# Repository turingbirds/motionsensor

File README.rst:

motionsensor
============

Microwave doppler effect motion sensor

Features
--------

- USB-powered (150 mA)
- Wakes up host computer on alarm (USB remote wakeup)
- Standalone operation (no PC or USB host required)
- Live velocity (IF) monitoring via USB audio stream to PC
- Automatic gain control
- Data logging
- Driverless operation: tested on Windows XP, Windows 7, Ubuntu GNU/Linux 14.04

..	

.. image:: doc/motionsensor2.jpeg
   :width: 1280
   :height: 780
   :scale: 60%
   :align: center

.. image:: doc/motionsensor3.jpeg
   :width: 1280
   :height: 780
   :scale: 60%
   :align: center

.. image:: doc/motionsensor1.jpeg
   :width: 1280
   :height: 780
   :scale: 60%
   :align: center

.. image:: doc/pcb.png
   :width: 1280
   :height: 811
   :scale: 60%
   :align: center

|

.. image:: doc/frontend_transfer_function.png
   :width: 846
   :height: 363
   :scale: 90%
   :align: center

|

.. image:: doc/doppler_log.png
   :width: 824
   :height: 386
   :scale: 93%
   :align: center

|

.. image:: doc/doppler_radio.png
   :width: 824
   :height: 414
   :scale: 93%
   :align: center

.. class:: center

All photos thanks to `Dennis van Zuijlekom <https://www.flickr.com/photos/dvanzuijlekom/>`_ at `Hack42 <http://www.hack42.nl>`_!

User guide
==========

Overview
--------

The device is based around a compact radar module. Radar waves penetrate glass and other materials, allowing the device to operate completely hidden from sight, unlike traditional passive infrared (PIR) motion detectors. The principle of operation for motion detection is the doppler effect. The module acts simultaneously as a sender and receiver of radar waves. Part of the emitted waves are reflected in the environment and fall back onto the sensor. If, meanwhile, an object in the environment has a motion component normal to the sensor, a doppler shift will be introduced in the reflected radio waves, proportional to the velocity of the object. The resulting frequency change (between emitted and received frequency) is demodulated by the module and output as a signal in the audio band. The rest of the device amplifies this signal and digitises it for further processing with the microcontroller and (optionally) relay to a connected USB host as an audio stream.

Many radar modules are commercially available for less than $10. This repository contains all the information necessary to build a complete USB/standalone motion detector based on such a module.

USB operation
-------------

The device uses a USB Interface Association Descriptor [1]_ to identify itself as (1) a standard HID-compliant mouse and (2) a standard USB streaming audio device. Only the HID can wake the computer.

Standalone operation
--------------------

The motion sensor does not require a USB host and can operate in standalone mode. For independent operation, supply power (4.5..14 V) via the USB GND and Vcc terminals.

When the alarm is raised, the USB D- line will be driven to +3.3V for at least 10 ms, after which it will return to a floating condition. The output impedance is at least 22 Ω due to the USB series resistor. If this line is used to drive external devices, it is advised to add a modest pull-down resistor (e.g. 4k7).

Host audio
==========

Linux
-----

In case of conflicts, remove interfering kernel drivers:

::

	sudo rmmod snd_usb_audio
	sudo rmmod snd_usbmidi_lib

Set volume levels and such:

::

	alsamixer

Find the motion sensor device:

::

	arecord -l

*Recording from the device:*

::

	arecord -f S16_LE -r 8000 -t raw -v -D hw:1,0 > foo.pcm

*Listening to the device:* This assumes that you are using pulseaudio.

::

	pactl load-module module-loopback latency_msec=1	

Windows XP
----------

*Recording from the device:* native, select "Microwave Doppler Sensor" as audio source

*Listening to the device:* Download "Virtual Audio Cable" [2]_ and use the "Audio Repeater" tool. Lag is at least 50 ms.

Windows 7
---------

*Recording from the device:* native

*Listening to the device:* native. Use "Listen to device" under [taskbar speaker icon] → Recording devices → Microwave Doppler Sensor → Properties → Listen → Listen to this device.

Host power management
=====================

N.B. USB wake needs to be enabled in BIOS

Linux
-----

Suspend using:

::

	pm-suspend

Find device in tree:

::

	grep -r Microwave /sys/devices/pci0000\:00/

In the ``power`` directory of the device, you'll find a file called ``wakeup``. Write "enabled" to this file, e.g.:

::

	echo "enabled" > /sys/devices/pci0000:00/0000:00:14.0/usb2/2-2/power/wakeup

Make sure to enable upstream hubs as well.

N.B. Add the commands in this section to ``/etc/rc.local`` to enable the wake-from-standby feature on boot.

Windows
-------

Enable "Allow device to wake computer from suspend" in the device manager properties of the HID-compatible mouse that is a part of the Microwave Doppler Sensor.

Developer's guide
=================

Frontend
--------

The frontend consists of a high-gain low-noise amplifier chain that is built using three dual op-amp ICs. The maximum theoretical voltage gain is 1.3·10\ :sup:`5` (100 dB). An 8-bit digital potentiometer after the second gain stage is configured as an attenuator and acts as gain control, with a dynamical range of 30 dB. The complete analog front-end is powered by a ±5V bipolar rail that is generated by an on-board boost converter. After amplification and filtering the signal is offered to a 12-bit ADC running at an 8 kHz sampling rate and 3.3 V reference voltage.

Data acquisition and USB communication is performed by an STM32F103 microcontroller. When connected to a USB host, the digital potentiometer setlevel is controlled by the volume setlevel of the device. When the volume is set to 100%, automatic gain control (AGC) is enabled. When not connected to USB, the potentiometer is set to a fixed value so that the frontend gain is high.

N.B. the AGC aliasing filter should be designed for one bit of noise at half the sampling rate, i.e. max. 0.81 mV @ 4 kHz (3.3 V across 12 bits = 0.81 mV/bit)

Firmware notes
--------------

For volume scale (how to map bits to decibels), see e.g. [3]_.

Schematic
---------

`Schematic (.pdf) <doc/motionsensor_schematic.pdf>`_

PCB
---

All discrete components are 0603.

- Dimensions: 78 x 49 mm
- Layers: 4 (two inner ground planes)
- Thickness: 1.2 mm

Enclosure and mounting
----------------------

Vertical cross-section:

::

	----USB/USER INTERFACE----
	- 5 mm plastic inserts (1.0 mm margin)
	- 1.2 mm main PCB
	- 5 mm bus
	- 1.2 mm shield PCB
	- 0.2 mm washer
	----DOPPLER UNIT----
	Total: 12 mm

Screw length: 12 mm
Screw diameter: 2.5 mm

N.B. Doppler module is <7 mm

Bill of materials
-----------------

`Bill of materials (.csv) <doc/bill_of_materials.csv>`_

References
==========

.. [1] USB Complete Fourth Edition: The Developer's Guide (4th edition). Jan Axelson, publisher: Lakeview Research. June 1, 2009
.. [2] `Virtual Audio Cable \<http://software.muzychenko.net/eng/vac.htm\> <http://software.muzychenko.net/eng/vac.htm>`_
.. [3] `USB audio device volume scale \<https://msdn.microsoft.com/en-us/library/windows/hardware/ff537309\> <https://msdn.microsoft.com/en-us/library/windows/hardware/ff537309(v=vs.85).aspx>`_

License
=======

`Open source hardware <https://www.oshwa.org/>`_ is hardware for which the design is made publicly available, so that anyone can study, modify, distribute, make, and sell the design or hardware based on that design, subject to the following license conditions.

Hardware licensed under the *CERN Open Hardware Licence Version 2 - Weakly Reciprocal,* a copy of which is included in this repository at `cern_ohl_w_v2.txt <https://github.com/turingbirds/motionsensor/blob/master/cern_ohl_w_v2.txt>`_.

Software licensed under the *Apache License 2.0,* a copy of which is included at `apache_license_2.0.txt <https://github.com/turingbirds/motionsensor/blob/master/apache_license_2.0.txt>`_.

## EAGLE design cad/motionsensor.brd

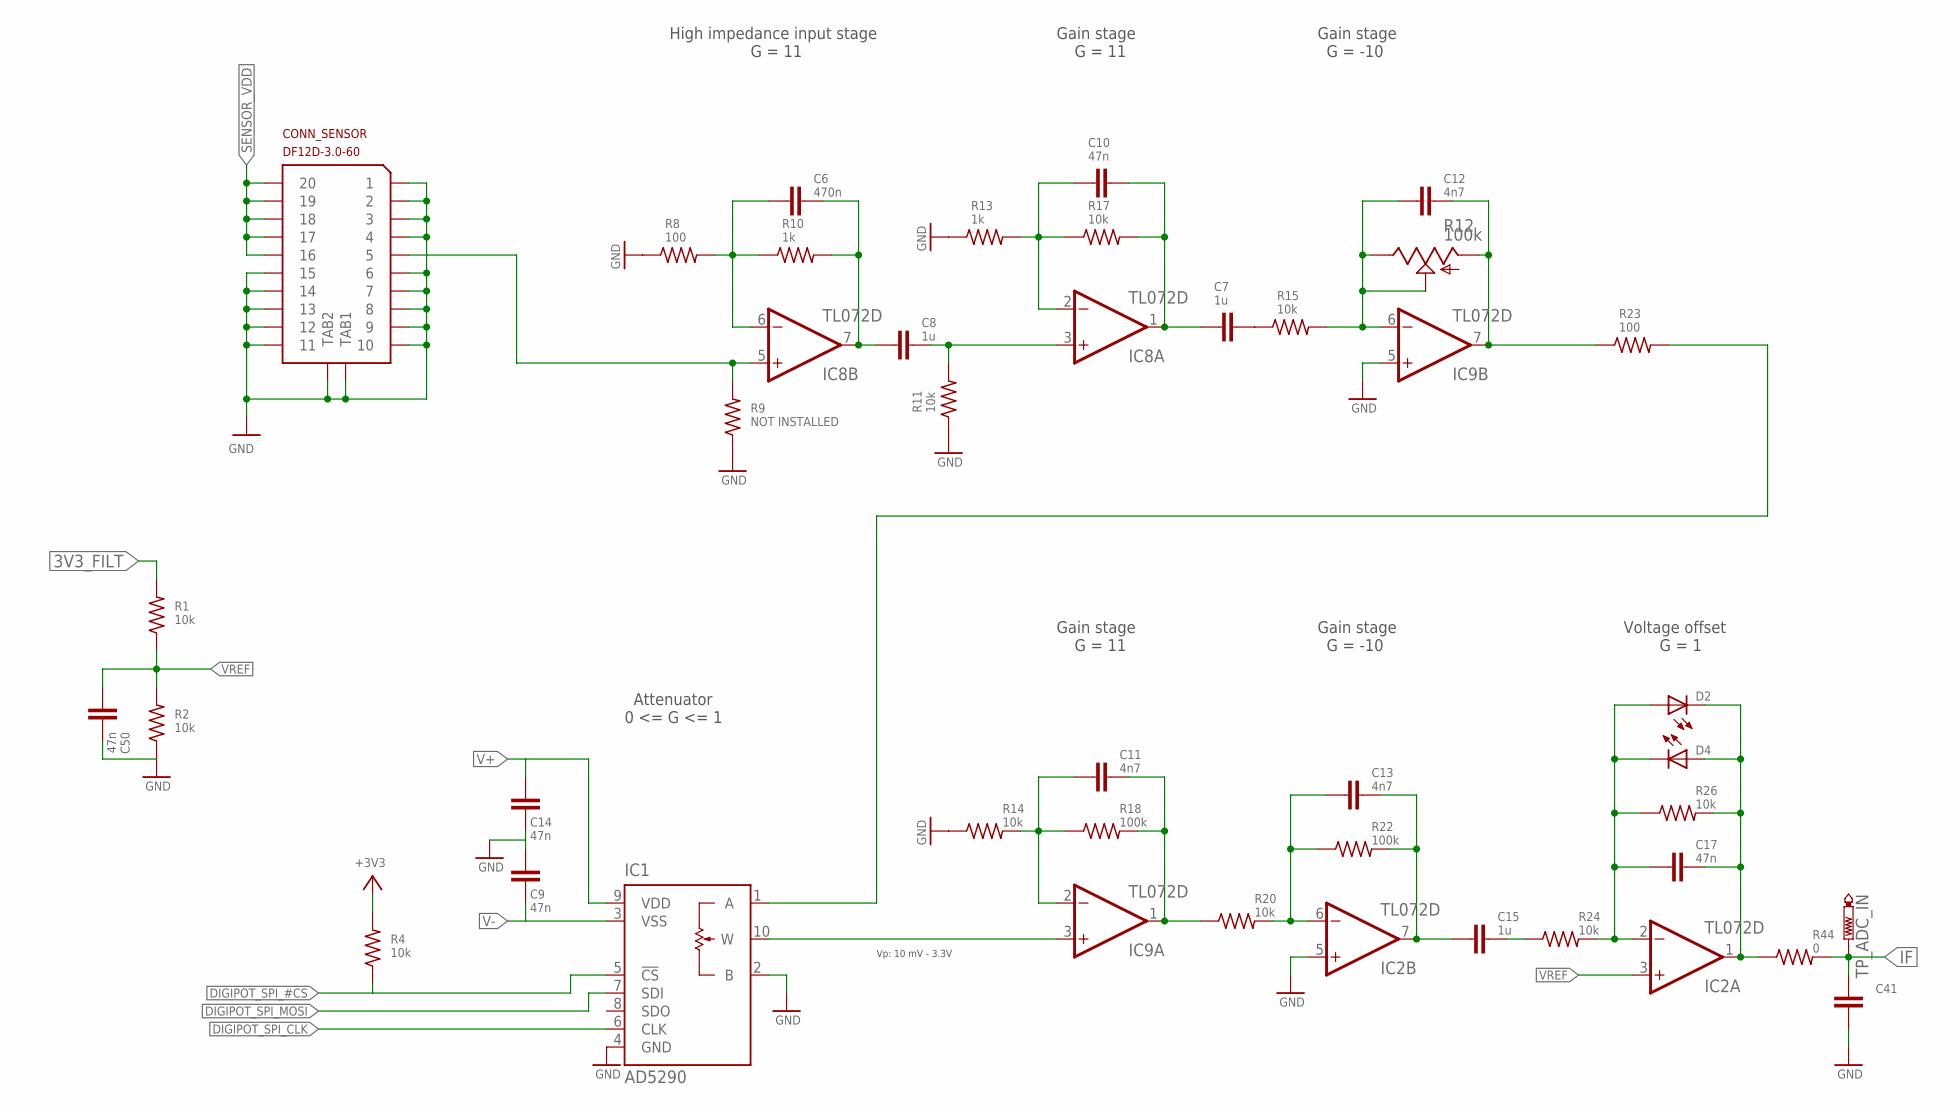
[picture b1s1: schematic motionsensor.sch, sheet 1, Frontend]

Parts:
C6: 470n; C0603
C7, C8, C15: 1u; C0603
C9, C10, C14, C17, C50: 47n; C0603
C11, C12, C13: 4n7; C0603
C41: C-EUC0603; C0603
CONN_SENSOR: DF12D-3.0-60; DF12-3.0-60
D2, D4: LEDCHIPLED_0603; CHIPLED_0603
IC1: AD5290; MSOP10
IC2, IC8, IC9: TL072D; SO08
R1, R2, R4, R11, R14, R15, R17, R20, R24, R26: 10k; R0603
R8, R23: 100; R0603
R9: NOT INSTALLED; R0603
R10, R13: 1k; R0603
R12: 100k; 3223G
R18, R22: 100k; R0603
R44: 0; R0603
TP_ADC_IN: PTR1B1,27; B1,27

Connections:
3V3_FILT: R1.2; also elsewhere on the board
+3V3: R4.2; also elsewhere on the board
DIGIPOT_SPI_#CS: IC1.5 (!CS), R4.1; also elsewhere on the board
DIGIPOT_SPI_CLK: IC1.6 (CLK); also elsewhere on the board
DIGIPOT_SPI_MOSI: IC1.7 (SDI); also elsewhere on the board
GND: C9.1, C14.2, C41.2, C50.2, CONN_SENSOR.P$1 (1), CONN_SENSOR.P$2 (2), CONN_SENSOR.P$3 (3), CONN_SENSOR.P$4 (4), CONN_SENSOR.P$6 (6), CONN_SENSOR.P$7 (7), CONN_SENSOR.P$8 (8), CONN_SENSOR.P$9 (9), CONN_SENSOR.P$10 (10), CONN_SENSOR.P$11 (11), CONN_SENSOR.P$12 (12), CONN_SENSOR.P$13 (13), CONN_SENSOR.P$14 (14), CONN_SENSOR.P$15 (15), CONN_SENSOR.TAB1, CONN_SENSOR.TAB2, IC1.2 (B), IC1.4 (GND), IC2.5 (+IN), IC9.5 (+IN), R2.1, R8.1, R9.1, R11.1, R13.1, R14.1; also elsewhere on the board
IF: C41.1, R44.2, TP_ADC_IN.TP; also elsewhere on the board
unnamed: C6.1, IC8.6 (-IN), R8.2, R10.1
unnamed: C6.2, C8.1, IC8.7 (OUT), R10.2
unnamed: CONN_SENSOR.P$5 (5), IC8.5 (+IN), R9.2
unnamed: C7.2, R15.1
unnamed: C10.1, IC8.2 (-IN), R13.2, R17.1
unnamed: C7.1, C10.2, IC8.1 (OUT), R17.2
unnamed: C8.2, IC8.3 (+IN), R11.2
unnamed: C12.1, IC9.6 (-IN), R12.2 (S), R12.3 (E), R15.2
unnamed: C12.2, IC9.7 (OUT), R12.1 (A), R23.1
unnamed: IC1.1 (A), R23.2
unnamed: C11.1, IC9.2 (-IN), R14.2, R18.1
unnamed: C11.2, IC9.1 (OUT), R18.2, R20.1
unnamed: C13.1, IC2.6 (-IN), R20.2, R22.1
unnamed: C13.2, C15.1, IC2.7 (OUT), R22.2
unnamed: C15.2, R24.1
unnamed: IC1.10 (W), IC9.3 (+IN)
unnamed: C17.1, D2.A, D4.C, IC2.2 (-IN), R24.2, R26.1
unnamed: C17.2, D2.C, D4.A, IC2.1 (OUT), R26.2, R44.1
SENSOR_VDD: CONN_SENSOR.P$16 (16), CONN_SENSOR.P$17 (17), CONN_SENSOR.P$18 (18), CONN_SENSOR.P$19 (19), CONN_SENSOR.P$20 (20); also elsewhere on the board
V+: C14.1, IC1.9 (VDD); also elsewhere on the board
V-: C9.2, IC1.3 (VSS); also elsewhere on the board
VREF: C50.1, IC2.3 (+IN), R1.1, R2.2

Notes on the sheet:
High impedance input stage
G = 11
Gain stage
G = -10
Voltage offset
G = 1
Attenuator
0 <= G <= 1
Vp: 10 mV - 3.3V

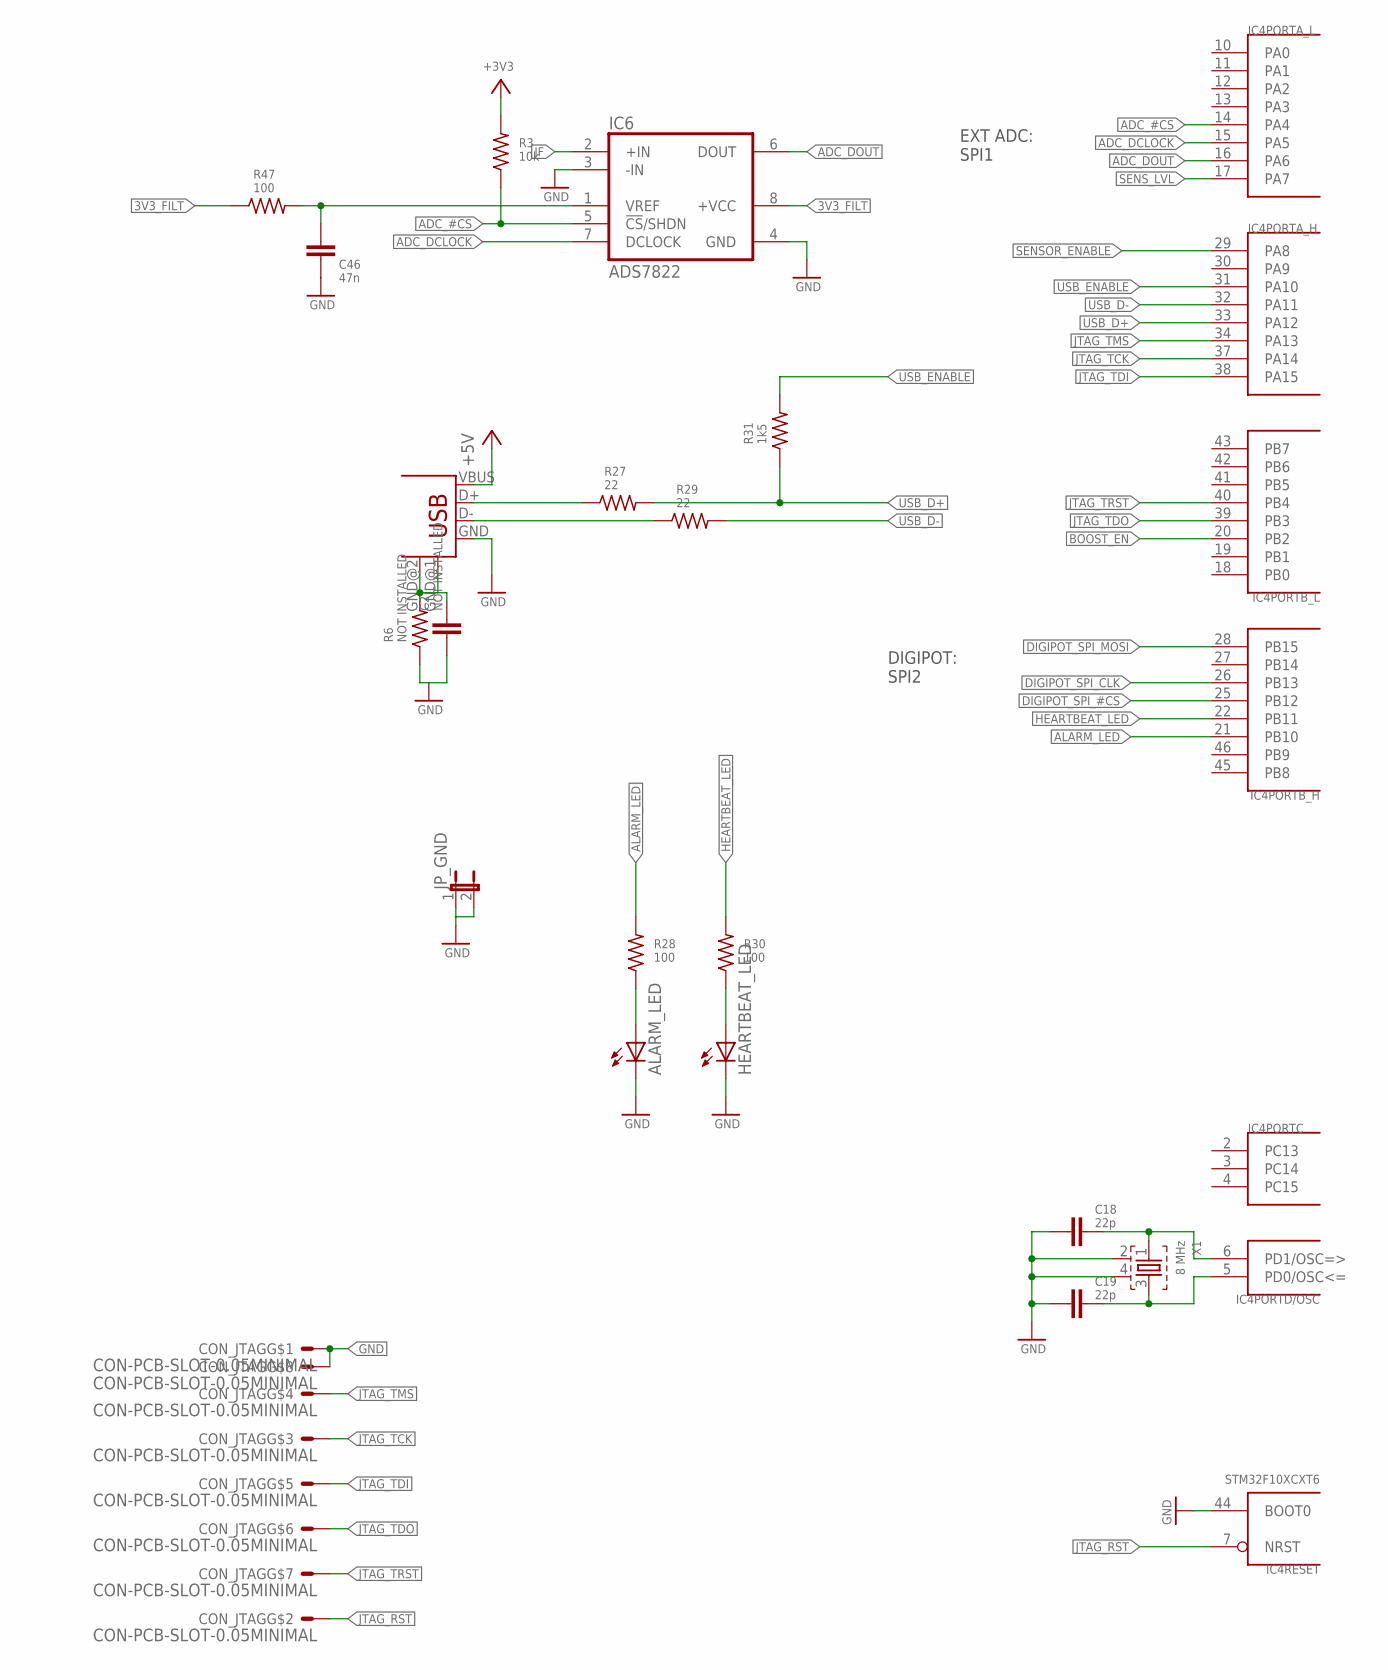
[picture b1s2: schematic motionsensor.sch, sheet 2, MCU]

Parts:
ALARM_LED: LED3MM
C2: NOT INSTALLED; C0603
C18, C19: 22p; C0603
C46: 47n; C0603
CON_JTAG: CON-PCB-SLOT-0.05MINIMAL; CONN_SLOT_MINIMAL
CON_USB: USB-VERT; USB-MB-V
HEARTBEAT_LED: LED3MM
IC4: STM32F10XCXT6; TQFP48
IC6: ADS7822; SO08
JP_GND: JP1E; JP1
R3: 10k; R0603
R6: NOT INSTALLED; R0603
R27, R29: 22; R0603
R28, R30, R47: 100; R0603
R31: 1k5; R0603
X1: 8 MHz; CTS406

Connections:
3V3_FILT: IC6.8 (+VCC), R47.1; also elsewhere on the board
+3V3: R3.2; also elsewhere on the board
ADC_#CS: IC4.14 (PA4), IC6.5 (!CS!/SHDN), R3.1
ADC_DCLOCK: IC4.15 (PA5), IC6.7 (DCLOCK)
ADC_DOUT: IC4.16 (PA6), IC6.6 (DOUT)
ALARM_LED: IC4.21 (PB10), R28.2
BOOST_EN: IC4.20 (PB2); also elsewhere on the board
DIGIPOT_SPI_#CS: IC4.25 (PB12); also elsewhere on the board
DIGIPOT_SPI_CLK: IC4.26 (PB13); also elsewhere on the board
DIGIPOT_SPI_MOSI: IC4.28 (PB15); also elsewhere on the board
GND: ALARM_LED.K (C), C2.1, C18.1, C19.1, C46.2, CON_JTAG.1, CON_JTAG.8, CON_USB.GND, HEARTBEAT_LED.K (C), IC4.44 (BOOT0), IC6.3 (-IN), IC6.4 (GND), JP_GND.1, JP_GND.2, R6.1, X1.2, X1.4; also elsewhere on the board
HEARTBEAT_LED: IC4.22 (PB11), R30.2
IF: IC6.2 (+IN); also elsewhere on the board
JTAG_RST: CON_JTAG.2, IC4.7 (NRST)
JTAG_TCK: CON_JTAG.3, IC4.37 (PA14)
JTAG_TDI: CON_JTAG.5, IC4.38 (PA15)
JTAG_TDO: CON_JTAG.6, IC4.39 (PB3)
JTAG_TMS: CON_JTAG.4, IC4.34 (PA13)
JTAG_TRST: CON_JTAG.7, IC4.40 (PB4)
unnamed: C2.2, CON_USB.GND@1 (GND), CON_USB.GND@2 (GND), R6.2
unnamed: CON_USB.D+, R27.1
unnamed: C46.1, IC6.1 (VREF), R47.2
unnamed: CON_USB.D-, R29.1
unnamed: C19.2, IC4.5 (PD0/OSC<=), X1.3
unnamed: C18.2, IC4.6 (PD1/OSC=>), X1.1
unnamed: ALARM_LED.A, R28.1
unnamed: HEARTBEAT_LED.A, R30.1
SENSOR_ENABLE: IC4.29 (PA8); also elsewhere on the board
SENS_LVL: IC4.17 (PA7)
USB_+5V: CON_USB.VBUS; also elsewhere on the board
USB_D+: IC4.33 (PA12), R27.2, R31.1
USB_D-: IC4.32 (PA11), R29.2
USB_ENABLE: IC4.31 (PA10), R31.2

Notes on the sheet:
EXT ADC: SPI1
DIGIPOT: SPI2

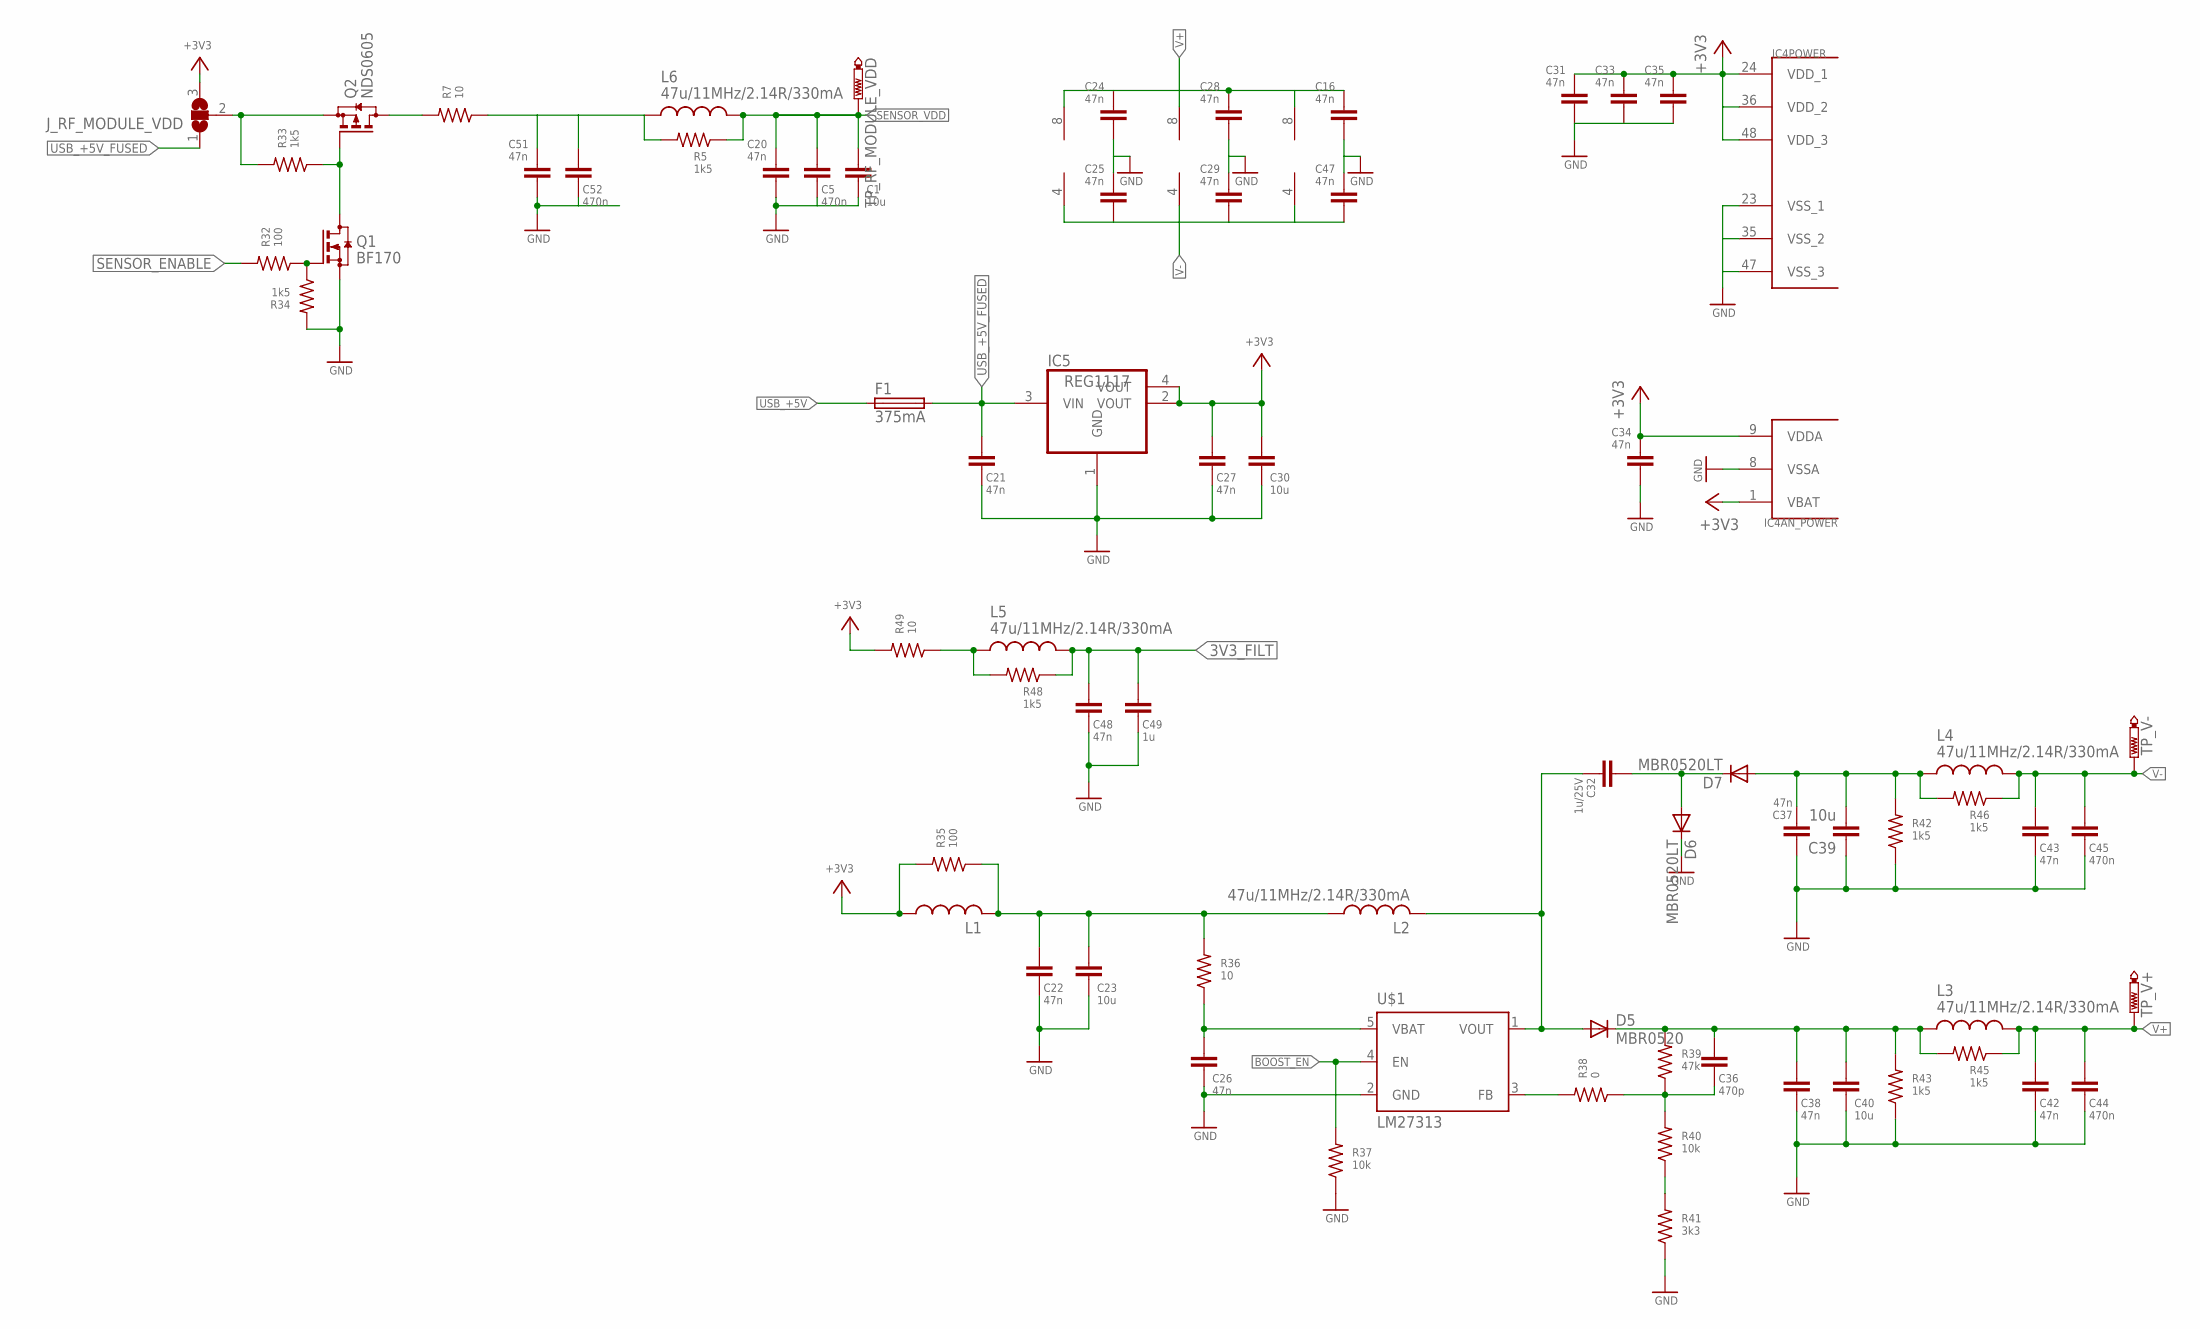
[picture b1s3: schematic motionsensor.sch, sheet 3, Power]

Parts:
C1, C23, C30, C39, C40: 10u; C1206
C5, C44, C45, C52: 470n; C0603
C16, C20, C21, C22, C24, C25, C27, C28, C29, C31, C33, C34, C35, C37, C38, C42, C43, C47, C48, C51: 47n; C0603
C26: 47n; C1206
C32: 1u/25V; C0603
C36: 470p; C0603
C49: 1u; C0603
D5: MBR0520; SOD123
D6, D7: MBR0520LT; SOD123
F1: 375mA; 0603
IC2, IC8, IC9: TL072D; SO08
IC4: STM32F10XCXT6; TQFP48
IC5: REG1117; SOT223
J_RF_MODULE_VDD: SJ2W; SJ_2
L1: L-USL2012C; L2012C
L2, L3, L4, L5, L6: 47u/11MHz/2.14R/330mA; R1210
Q1: BF170; SOT23
Q2: NDS0605; SOT23
R5, R33, R34, R42, R43, R45, R46, R48: 1k5; R0603
R7, R36, R49: 10; R0603
R32, R35: 100; R0603
R37, R40: 10k; R0603
R38: 0; R0603
R39: 47k; R0603
R41: 3k3; R0603
TP_RF_MODULE_VDD: PTR1B1,27; B1,27
TP_V+: PTR1B1,27; B1,27
TP_V-: PTR1B1,27; B1,27
U$1: LM27313; TSOP5

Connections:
3V3_FILT: C48.1, C49.1, L5.2, R48.1; also elsewhere on the board
+3V3: C27.1, C30.1, C31.2, C33.2, C34.2, C35.2, IC4.1 (VBAT), IC4.9 (VDDA), IC4.24 (VDD_1), IC4.36 (VDD_2), IC4.48 (VDD_3), IC5.2 (VOUT), IC5.4 (VOUT), J_RF_MODULE_VDD.3, L1.1, R35.2, R49.2; also elsewhere on the board
+3V3_FILT: C22.1, C23.1, L1.2, L2.1, R35.1, R36.2
BOOST_EN: R37.2, U$1.4 (EN); also elsewhere on the board
GND: C1.2, C5.2, C16.1, C20.1, C21.2, C22.2, C23.2, C24.1, C25.2, C26.2, C27.2, C28.1, C29.2, C30.2, C31.1, C33.1, C34.1, C35.1, C37.1, C38.2, C39.1, C40.2, C42.2, C43.2, C44.2, C45.2, C47.2, C48.2, C49.2, C51.1, C52.2, D6.C, IC4.8 (VSSA), IC4.23 (VSS_1), IC4.35 (VSS_2), IC4.47 (VSS_3), IC5.1 (GND), Q1.2 (S), R34.2, R37.1, R41.1, R42.1, R43.1, U$1.2 (GND); also elsewhere on the board
unnamed: J_RF_MODULE_VDD.2, Q2.2 (S), R33.2
unnamed: Q2.3 (D), R7.2
unnamed: Q1.1 (G), R32.1, R34.1
unnamed: L5.1, R48.2, R49.1
unnamed: Q1.3 (D), Q2.1 (G), R33.1
unnamed: C32.2, D5.A, L2.2, U$1.1 (VOUT)
unnamed: C26.1, R36.1, U$1.5 (VBAT)
unnamed: C32.1, D6.A, D7.C
unnamed: C36.2, R38.1, R39.1, R40.2
unnamed: R40.1, R41.2
unnamed: R38.2, U$1.3 (FB)
unnamed: C37.2, C39.2, D7.A, L4.1, R42.2, R46.2
unnamed: C36.1, C38.1, C40.1, D5.C, L3.1, R39.2, R43.2, R45.2
SENSOR_ENABLE: R32.2; also elsewhere on the board
SENSOR_VDD: C1.1, C5.1, C20.2, L6.2, R5.1, TP_RF_MODULE_VDD.TP; also elsewhere on the board
SENSOR_VDD1: C51.2, C52.1, L6.1, R5.2, R7.1
USB_+5V: F1.1; also elsewhere on the board
USB_+5V_FUSED: C21.1, F1.2, IC5.3 (VIN), J_RF_MODULE_VDD.1
V+: C16.2, C24.2, C28.2, C42.1, C44.1, IC2.8 (V+), IC8.8 (V+), IC9.8 (V+), L3.2, R45.1, TP_V+.TP; also elsewhere on the board
V-: C25.1, C29.1, C43.1, C45.1, C47.1, IC2.4 (V-), IC8.4 (V-), IC9.4 (V-), L4.2, R46.1, TP_V-.TP; also elsewhere on the board

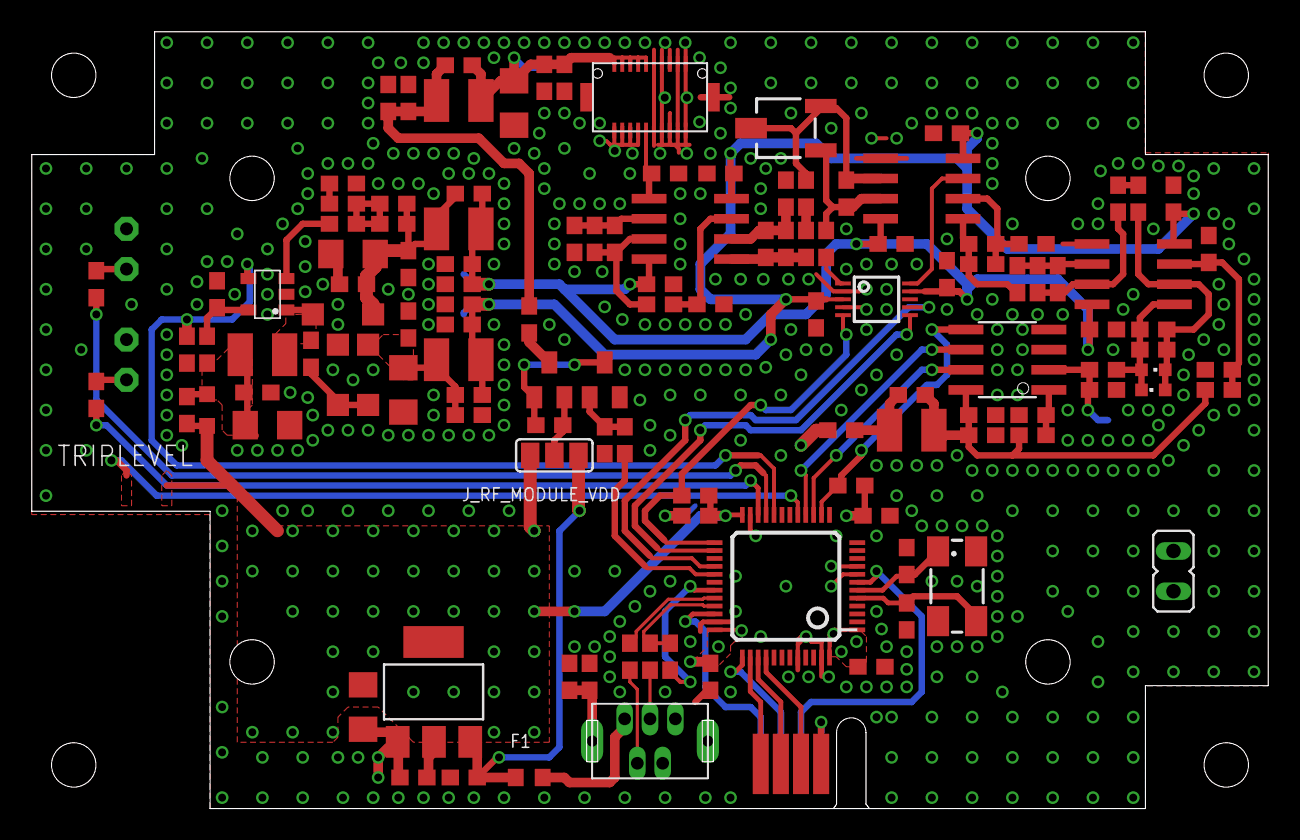
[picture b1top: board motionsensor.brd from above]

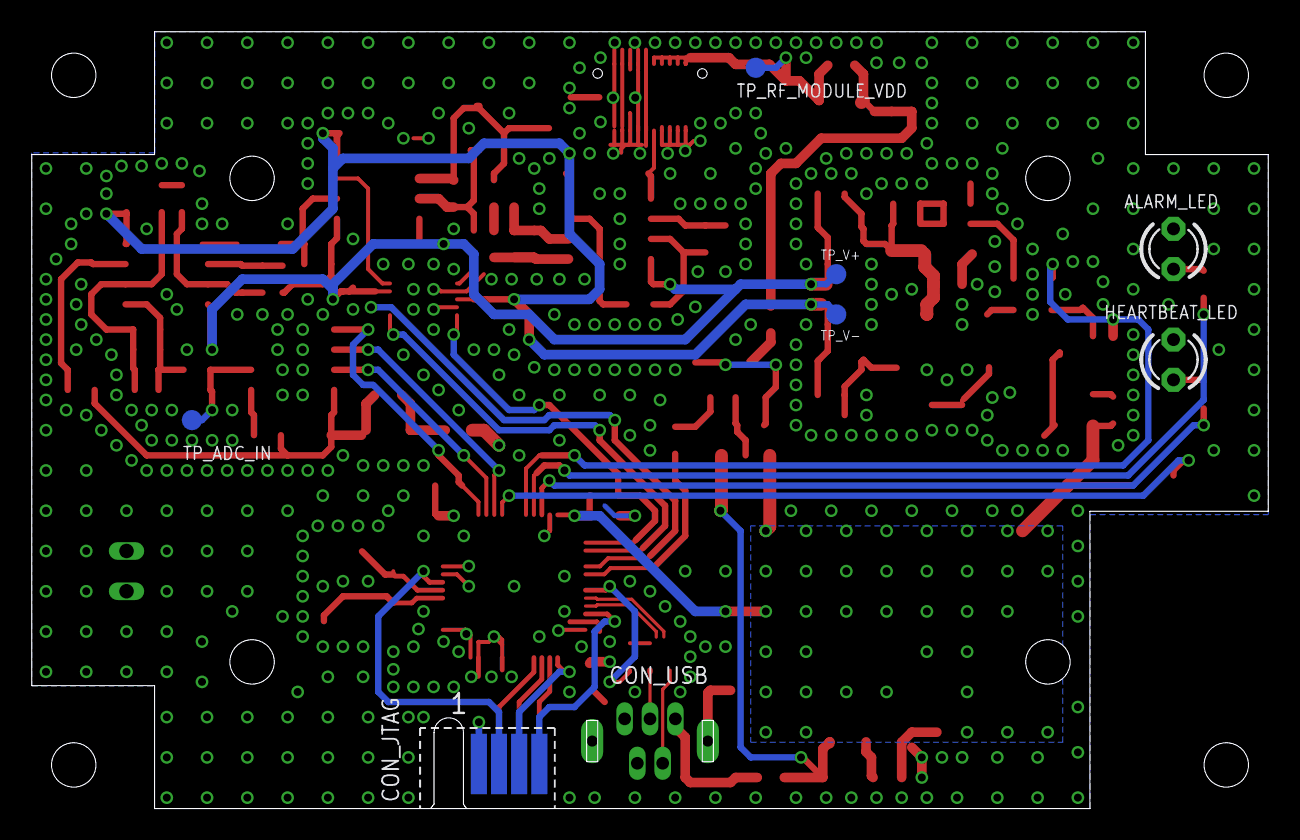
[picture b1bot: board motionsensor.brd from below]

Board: 4 copper layers, 78.0 x 49.0 mm, 129 parts (8 on the bottom side), 70 nets.

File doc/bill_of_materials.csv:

"Qty","Identifier","Description","Value","Package","Mouser #",,,,,,,,
,,"RESISTOR","NOT INSTALLED","0603",,,,,,,,,
"2","R38, R44","RESISTOR","0","0603",,,,,,,,,
"3","R7, R36, R49","RESISTOR","10","0603",,,,,,,,,
"2","R27, R29","RESISTOR","22","0603",,,,,,,,,
"7","R8, R23, R28, R30, R32, R35, R47","RESISTOR","100","0603",,,,,,,,,
"2","R10, R13","RESISTOR","1k","0603",,,,,,,,,
"7","R5, R31, R33, R34, R43, R45, R48","RESISTOR","1k5","0603",,,,,,,,,
"13","R1, R2, R3, R4, R11, R14, R15, R17, R20, R24, R26, R37, R40","RESISTOR","10k","0603",,,,,,,,,
"1","R41","RESISTOR","3k3","0603",,,,,,,,,
"1","R39","RESISTOR","47k","0603",,,,,,,,,
"2","R18, R22","RESISTOR","100k","0603",,,,,,,,,
,,,,,,,,,,,,,
,"C5","CAPACITOR","NOT INSTALLED","0603",,,,,,,,,
"2","C18, C19","CAPACITOR","22p","0603",,,,,,,,,
"1","C36","CAPACITOR","470p","0603",,,,,,,,,
"3","C11, C12, C13, ","CAPACITOR","4n7","0603",,,,,,,,,
"27","C9, C10, C14, C16, C17, C20, C21, C22, C24, C25, C26, C27, C28, C29, C31, C33, C34, C35, C37, C38, C42, C43, C46, C47, C48, C50, C51","CAPACITOR","47n","0603",,,,,,,,,
"5","C5, C6, C44, C45, C52","CAPACITOR","470n","0603",,,,,,,,,
"3","C7, C8, C15, ","CAPACITOR","1u","0603",,,,,,,,,
"4","C23, C30, C39, C40","CAPACITOR","10u","1206","581-TCJA106M16R200",,,,,,,,
,,,,,,,,,,,,,
"5","L1","INDUCTOR","47u/11MHz/2.5R/35mA","0603","963-LBMF1608T470K",,,,,,,,
"1","L2","INDUCTOR","47u/11MHz/2.14R/330mA","1210","815-AISC-1210H-470K",,,,,,,,
,,,,,,,,,,,,,
"2","ALARM_LED, HEARTBEAT_LED","LED","GREEN THROUGH-HOLE","3 mm",,,,,,,,,
"2","D2, D4","LED","INFRARED 1.6 V","0603","604-APT1608F3C",,,,,,,,
"3","D5, D6, D7","DIODE","MBR0520","SOD-123","512-MBR0520L",,,,,,,,
,,,,,,,,,,,,,
"1","Q1","N-CHANNEL MOSFET","BF170","SOT-23",,,,,,,,,
"1","Q2","P-CHANNEL MOSFET","NDS0605","SOT-23",,,,,,,,,
,,,,,,,,,,,,,
"1","IC1","IC","AD5290-10k","MSOP-10","584-AD5290YRMZ10",,,,,,,,
"1","U$1","IC","LM27313","TSOP-5","926-LM27313XMF/NOPB",,,,,,,,
"2","IC2, IC3","IC","LM324D","SOIC-14","595-LM324ADR",,,,,,,,
"1","IC5","IC","LM1117","SOT-232","926-LM1117MPX3.3NOPB",,,,,,,,
"1","IC4","IC","STM32F103","LQFP-48","511-STM32F103CBT6",,,,,,,,
,,,,,,,,,,,,,
"1","F1","FUSE","375mA","0603","581-F0603E0R37FSTR",,,,,,,,
"1","X1","XTAL","8 MHz","CTS406 (5 x 3.2 mm)","815-ABM3B-8.0-B2-T",,,,,,,,
"1",,"POTENTIOMETER","5k LINEAR","PANEL MOUNT","652-3310P-101-502L","Wiper resistance not critical; can also use 10k",,,,,,,
"1",,"POTENTIOMETER KNOB","RED",,"450-0125","For black version: 450-0125",,,,,,,
"1","R12","POTENTIOMETER","100k LINEAR","3223 SMD",,,,,,,,,
,,,,,,,,,,,,,
"1","CONN_USB","CONN","USB-MINI","VERTICAL","538-500075-0517",,,,,,,,
"1","CONN_SENSOR_","CONN","HIROSE HEADERS","20 way, height: 5 mm","798-DF125020DP0.5V86",,,,,,,,
"1","CONN_SENSOR","CONN","HIROSE RECEPTACLE","20 way, height: 5 mm","798-DF12-20DS-0.5V86",,,,,,,,
,,,,,,,,,,,,,
"1",,"ENCLOSURE","HAMMOND","1591XXLSBK (2.4 x 2.2 x 1.4 inch)","546-1591XXLSBK",,,,,,,,"546-1591XXLSBK"
"4",,"STANDOFFS","M2.5; 5 mm",,"761-M0504-25-AL",,,,,,,,
"4",,"SCREWS","M2.5; 12 mm",,"534-29304",,,,,,,,
"4",,"WASHERS","M2.5",,,,,,,,,,

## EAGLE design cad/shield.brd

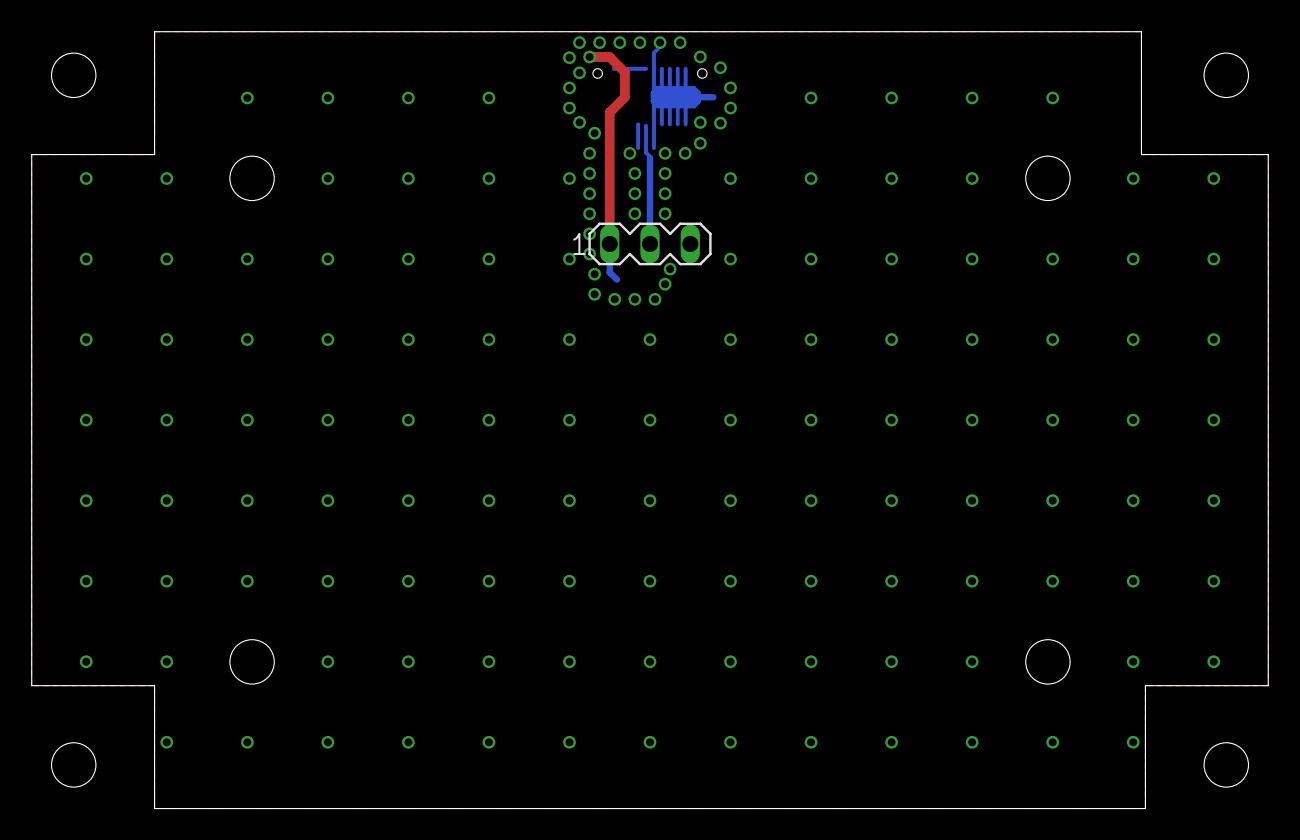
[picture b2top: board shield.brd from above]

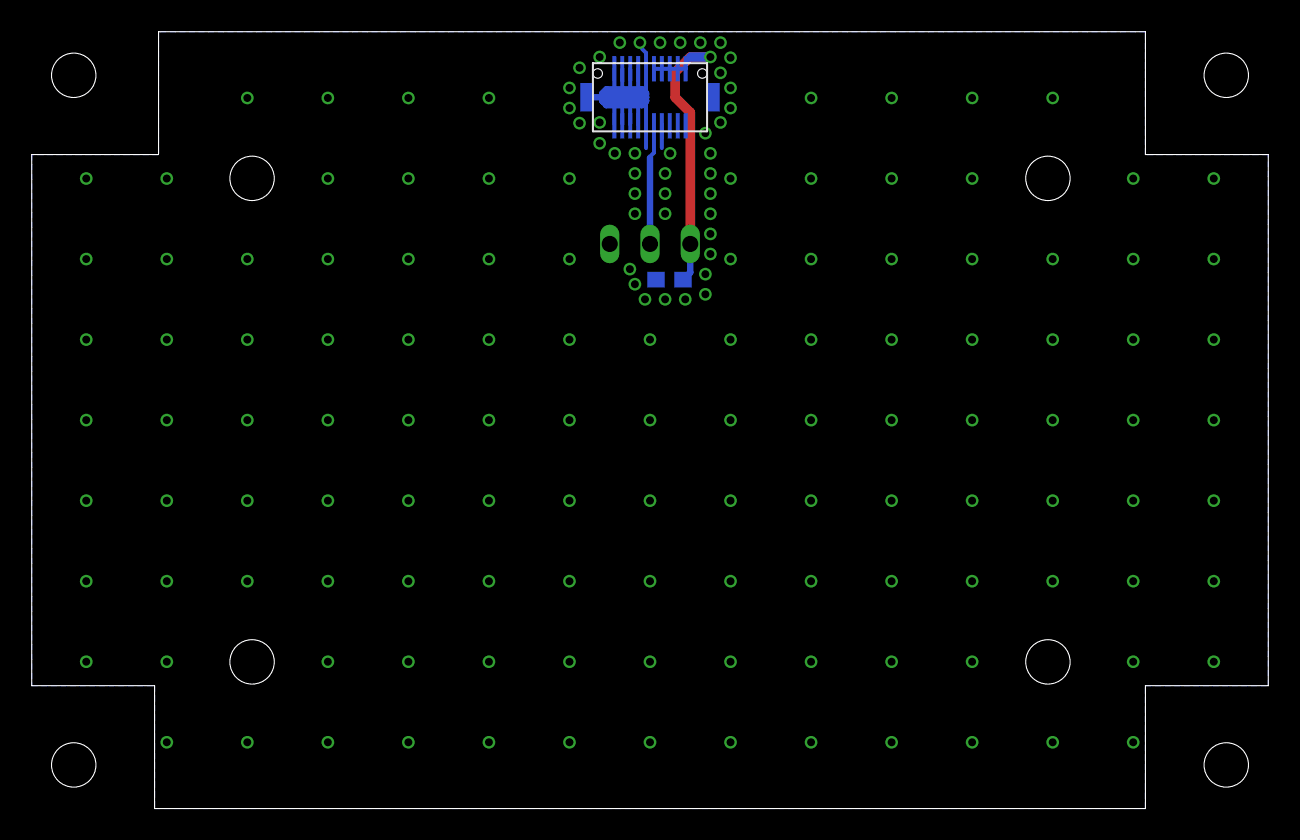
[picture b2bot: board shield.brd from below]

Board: 4 copper layers, 78.0 x 49.0 mm, 3 parts (2 on the bottom side), 3 nets.

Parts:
C1: 47n; C0603
CONN_SENSOR1: MA03-1
E$1: DF12-3.0-60

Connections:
+3V3: C1.1, CONN_SENSOR1.1, E$1.P$11, E$1.P$12, E$1.P$13, E$1.P$14, E$1.P$15
GND: C1.2, CONN_SENSOR1.3, E$1.P$1, E$1.P$2, E$1.P$3, E$1.P$4, E$1.P$5, E$1.P$7, E$1.P$8, E$1.P$9, E$1.P$10, E$1.P$16, E$1.P$17, E$1.P$18, E$1.P$19, E$1.P$20, E$1.TAB1, E$1.TAB2
S$1: CONN_SENSOR1.2, E$1.P$6

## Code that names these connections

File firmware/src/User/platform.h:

#ifndef PLATFORM_H
#define PLATFORM_H

#include <stdlib.h>

#include "stm32f10x.h"
#include "stm32f10x_dma.h"
#include "stm32f10x_adc.h"
#include "stm32f10x_spi.h"
#include "usb_lib.h"
#include "usb_pwr.h"
#include "usb_type.h"
#include "usb_desc.h"
#include "cyccnt_delay.h"


#define BIT_SET(a,b) ((a) |= (1<<(b-1)))
#define BIT_CLEAR(a,b) ((a) &= ~(1<<(b-1)))
#define BIT_FLIP(a,b) ((a) ^= (1<<(b-1)))
#define BIT_CHECK(a,b) ((a) & (1<<(b-1)))

#define BITMASK_SET(x,y) ((x) |= (y))
#define BITMASK_CLEAR(x,y) ((x) &= (~(y)))
#define BITMASK_FLIP(x,y) ((x) ^= (y))
#define BITMASK_CHECK(x,y) ((x) & (y))

#ifdef __GNUC__
/* With GCC/RAISONANCE, small printf (option LD Linker->Libraries->Small printf
   set to 'Yes') calls __io_putchar() */
#define PUTCHAR_PROTOTYPE int __io_putchar(int ch)
#else
#define PUTCHAR_PROTOTYPE int fputc(int ch, FILE *f)
#endif /* __GNUC__ */

#define LO(v)   ((unsigned char) (v))
#define HI(v)  ((unsigned char) (((unsigned int) (v)) >> 8))

#define MIN(a,b) (((a)<(b))?(a):(b))
#define MAX(a,b) (((a)>(b))?(a):(b))

#define true		1
#define false		0


/**
 * data buffers
**/

#define ADC_BUFFER_SIZE 256

// clip level is defined with respect to the range of `input_level`, i.e. [0..FFFF].
#define CLIP_HIGHER_LEVEL			((uint16_t)(0x7FFF))
#define CLIP_LOWER_LEVEL			((uint16_t)(0x0FFF))


/**
 *	interrupt priority levels (low number = high priority)
**/

#define TIM3_INTR_PRIO				((uint8_t)0x00)
#define SPI1_INTR_PRIO 				((uint8_t)0x00)
#define USB_HP_INTR_PRIO			((uint8_t)0x01)
#define USB_LP_INTR_PRIO			((uint8_t)0x01)
#define TIM1_INTR_PRIO				((uint8_t)0x03)
#define ADC1_2_INTR_PRIO			((uint8_t)0x04)


/**
 *	activity LED
**/
#define LED_PWM_PORT										GPIOB
#define LED_PWM_PIN											GPIO_Pin_11
#define LED_PWM_GPIO_CLOCK_DOMAIN_AF		RCC_APB2Periph_AFIO
#define LED_PWM_GPIO_CLOCK_DOMAIN				RCC_APB2Periph_GPIOB


/**
 *	alarm LED
**/

#define LED_ALARM_PORT										GPIOB
#define LED_ALARM_PIN											GPIO_Pin_10
#define LED_ALARM_GPIO_CLOCK_DOMAIN				RCC_APB2Periph_GPIOB


/**
 *	 boost converter clock generator
**/

#define BOOST_OSC_PORT										GPIOB
#define BOOST_OSC_PIN											GPIO_Pin_2
#define BOOST_OSC_GPIO_CLOCK_DOMAIN_AF		RCC_APB2Periph_AFIO
#define BOOST_OSC_GPIO_CLOCK_DOMAIN				RCC_APB2Periph_GPIOB


/**
 *	output pin for turning the RF module on/off
**/

#define RF_MODULE_PWR_CONTROL_GPIO_PORT											GPIOA
#define RF_MODULE_PWR_CONTROL_GPIO_PIN											GPIO_Pin_8
#define RF_MODULE_PWR_CONTROL_GPIO_CLOCK_DOMAIN				RCC_APB2Periph_GPIOA


/**
 *	digital potentiometer via SPI2
**/

#define DIGIPOT_SPI_PORT			GPIOB
#define DIGIPOT_SPI_CLK_PIN		GPIO_Pin_13
#define DIGIPOT_SPI_MOSI_PIN	GPIO_Pin_15
#define DIGIPOT_SPI_CS_PIN		GPIO_Pin_12

#define WIPER_POS_STARTUP			0x0F
#define MAX_BLINK_PERIOD 	0x1F
#define MAX_WIPER_POS 255		// use to limit gain


/**
 *	external ADC via SPI1
**/

#define EXTERNAL_ADC_GPIO_CLK_DOMAIN	RCC_APB2Periph_GPIOA
#define EXTERNAL_ADC_PORT		GPIOA
#define EXTERNAL_ADC_CLK_PIN		GPIO_Pin_5
#define EXTERNAL_ADC_DOUT_PIN		GPIO_Pin_6
#define EXTERNAL_ADC_CS_PIN			GPIO_Pin_4


/**
 *	USB enable line
 *
 *	assumed active-high (change in platform.c:USB_Cable_Config)
**/

#define USB_ENBL_PORT										GPIOA
#define USB_ENBL_PIN										GPIO_Pin_10
//#define USB_ENBL_PIN										GPIO_Pin_2		# for PORT103Z
#define USB_ENBL_CLOCK_DOMAIN						RCC_APB2Periph_GPIOA
#define USB_GPIO_CLOCK_DOMAIN		RCC_APB2Periph_GPIOA
#define USB_PORT					GPIOA
#define USB_DN_PIN				GPIO_Pin_11

#define ADC_ALARM_PORT							GPIOA
#define ADC_ALARM_PIN									GPIO_Pin_7
#define ADC_ALARM_PIN_CLOCK_DOMAIN_AF	RCC_APB2Periph_AFIO
#define ADC_ALARM_PIN_CLOCK_DOMAIN			RCC_APB2Periph_GPIOA
#define ADC_ALARM_CHANNEL			ADC_Channel_7		// N.B. ADC_Channel_17 is internal ref

/* ------------------------------------------------------------------------- */

#define RCC_APB2Periph_ALLGPIO             (RCC_APB2Periph_GPIOA \
																						| RCC_APB2Periph_GPIOB \
																						| RCC_APB2Periph_GPIOC \
																						| RCC_APB2Periph_GPIOD \
																						| RCC_APB2Periph_GPIOE )

/* ------------------------------------------------------------------------- */

void platform_init(void);
void set_LED_brightness(uint8_t val);
void Set_USBClock(void);
void GPIO_AINConfig(void);
void GPIO_init(void);
void NVIC_Configuration(void);
int16_t grab_adc_sample(void);
void Enter_LowPowerMode(void);
void Leave_LowPowerMode(void);
void USB_Interrupts_Config(void);
void USB_Cable_Config (FunctionalState NewState);
void set_wiper(uint8_t val);
uint16_t read_alarm_setlevel(void);
void set_alarm_enable(uint8_t _alarm_enable);

/* ------------------------------------------------------------------------- */

#endif

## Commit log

2017-02-15 beta version release
2017-02-15 fixed typo
2017-02-15 cleanup readme
2018-08-15 cleaned up obsolete files
2022-02-06 add license information
